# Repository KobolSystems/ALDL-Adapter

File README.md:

## USB ALDL Adapter 

### **Project**: ALDL to USB Adapter 

<!-- Repo Cover Image -->

<!-- Repo Stats -->

<!-- Other Intro -->
### What is a ALDL
Assembly Line Diagnostic Link or ALDL is a proprietary on-board diagnostics system developed by General Motors before the standardization of OBD-2. It was previously called Assembly Line Communications Link or ALCL. The two terms are used interchangeably.

This system was only vaguely standardized and suffered from the fact that specifications for the communications link varied from one model to the next. ALDL was largely used by manufacturers for diagnostics at their dealerships and official maintenance facilities. The connector is usually located under the dash on the driver's side of left-hand drive (LHD) vehicles, though this location was not standardized.

The earliest implementations of ALDL were unidirectional and transmitted serial data at 160 baud using PWM. Some 160 baud models constantly transmitted sensor data on startup, while others started transmitting data when placed in diagnostic mode with a resistor connected to the ALDL port.

Later versions were bidirectional and operated at a much faster (but incredibly slow compared to today's standards) rate of 8192 baud. Implementations using the 8192 baud rate were primarily request-driven, meaning that the main diagnostic data was not transmitted until a request was made. Some idle data transmission of trivial parameters, however, existed in many vehicles. Bidirectional communication also allowed many other functions to be performed via ALDL, such as actuator tests, parameter overrides, and in some cases even reprogramming of the ECU itself. Multiple devices could be placed on the ALDL data line for primitive networking and communication. Many later 8192 baud vehicles, for example, had airbag control, ABS, and even climate control units sending data on the same serial bus.

In both versions, ALDL data is sent in a format unique to the model of ECU in the vehicle with little standardization between models, so a proper definition of the data is required to interpret it. Most professional scan tools require a large database of vehicle definitions.

The signaling of ALDL is similar to the RS-232 serial data standard; differing in the voltages used to denote logical one (usually 0 V DC) and logical zero (either +5 V DC or +12 V DC), and that unlike RS-232, both transmit and receive functions are on the same conductor. Schematics are available on the internet for devices that can be used to convert the ALDL voltages to those of the RS-232 standard, allowing the raw data to be read with a computer having a serial port and the proper software.

<!-- Version History -->
### Version History
|	Version	|	Status	|
|---------------|---------------|
|V.1.0		|Superseded	|
|V.2.0		|In Production	|

<!-- To Do List -->
### Project To Do List
- [ ] List Items Here

### Repo To Do List
- [x] Add V1.0 to Repo
- [ ] Add V1.0 Backplane to Repo
- [ ] Add V2.0 to Repo

<!-- Licencing Always at the Bottom -->
### Licencing 

**Creative Commons: Attribution - NonCommercial - ShareAlike 4.0 International (CC BY-NC-SA 4.0)**

**You are free to:**

**Share** — copy and redistribute the material in any medium or format

**Adapt** — remix, transform, and build upon the material

**Under the following terms:**

**Attribution** — You must give appropriate credit, provide a link to the license, and indicate if changes were made. You may do so in any reasonable manner, but not in any way that suggests the licensor endorses you or your use.

**NonCommercial** — You may not use the material for commercial purposes.

**ShareAlike** — If you remix, transform, or build upon the material, you must distribute your contributions under the same license as the original.

No additional restrictions — You may not apply legal terms or technological measures that legally restrict others from doing anything the license permits.

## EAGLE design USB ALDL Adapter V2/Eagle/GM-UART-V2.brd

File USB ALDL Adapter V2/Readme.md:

## USB ALDL Adapter V2.0  

### **Project**: ALDL to USB Adapter 

<!-- Repo Cover Image -->

<!-- PCB Image -->

### Adapter PCB

### PCB Bill of Materials
Part  |Value      |Device     	|Package          |Description                          	|Mouser Part 	     	|
------|-----------|-------------|-----------------|-----------------------------------------|-----------------------|
C1    |100nF      |C-EUC0603K 	|C0603K           |MLCC - SMD/SMT 100nF 50V               	|603-CC603ZPY5V9BB104   |   
C2    |10nF       |C-EUC0603K 	|C0603K           |MLCC - SMD/SMT 10nF 50V X7R 10%        	|603-CC603KRX7R9BB103   |   
C3    |47pF       |C-EUC0603K 	|C0603K           |MLCC - SMD/SMT 47pF 5% 50V             	|791-MT18N470J500CT     |   
C4    |47pF       |C-EUC0603K 	|C0603K           |MLCC - SMD/SMT 47pF 5% 50V             	|791-MT18N470J500CT     |   
D1    |1N4148     |1N4148W-E3-18|SOD-123	  	  |Diode 100 Volt 500mA 4ns					|78-1N4148W-E3-18       |                              
IC1   |FT230XQ    |FT230XQ    	|QFN16            |USB to BASIC UART IC                   	|895-FT230XQ-R          |                            
R1    |1KR        |R-US_M0805 	|M0805            |Resistor - SMD 1/4watts 1Kohms 1%      	|660-RK73H2ATTD1001F    |   
R3    |27R        |R-US_R0603 	|R0603            |Resistor - SMD 1/20watt 27ohms 5%      	|71-CRCW020127R0JNED    |   
R4    |27R        |R-US_R0603	|R0603            |Resistor - SMD 1/20watt 27ohms 5%      	|71-CRCW020127R0JNED    |   
SV1   |USB-CONN   |MA04-1     	|MA04-1           |PIN HEADER                             	|NOT POPULATED          |  
U$1   |OBD2       |OBD2       	|OBD2             |OBDII Connector                        	|NOT POPULATED		    |     

<!-- To Do List -->
### Repo To Do List
- [x] Create Readme.md
- [ ] Update Readme Image to Actual V2
- [x] Add Eagle Files
- [x] Add .PDF Schematic
- [ ] Add Board Pics

<!-- Licencing Always at the Bottom -->
### Licencing 

**Creative Commons: Attribution - NonCommercial - ShareAlike 4.0 International (CC BY-NC-SA 4.0)**

**You are free to:**

**Share** — copy and redistribute the material in any medium or format

**Adapt** — remix, transform, and build upon the material

**Under the following terms:**

**Attribution** — You must give appropriate credit, provide a link to the license, and indicate if changes were made. You may do so in any reasonable manner, but not in any way that suggests the licensor endorses you or your use.

**NonCommercial** — You may not use the material for commercial purposes.

**ShareAlike** — If you remix, transform, or build upon the material, you must distribute your contributions under the same license as the original.

No additional restrictions — You may not apply legal terms or technological measures that legally restrict others from doing anything the license permits.

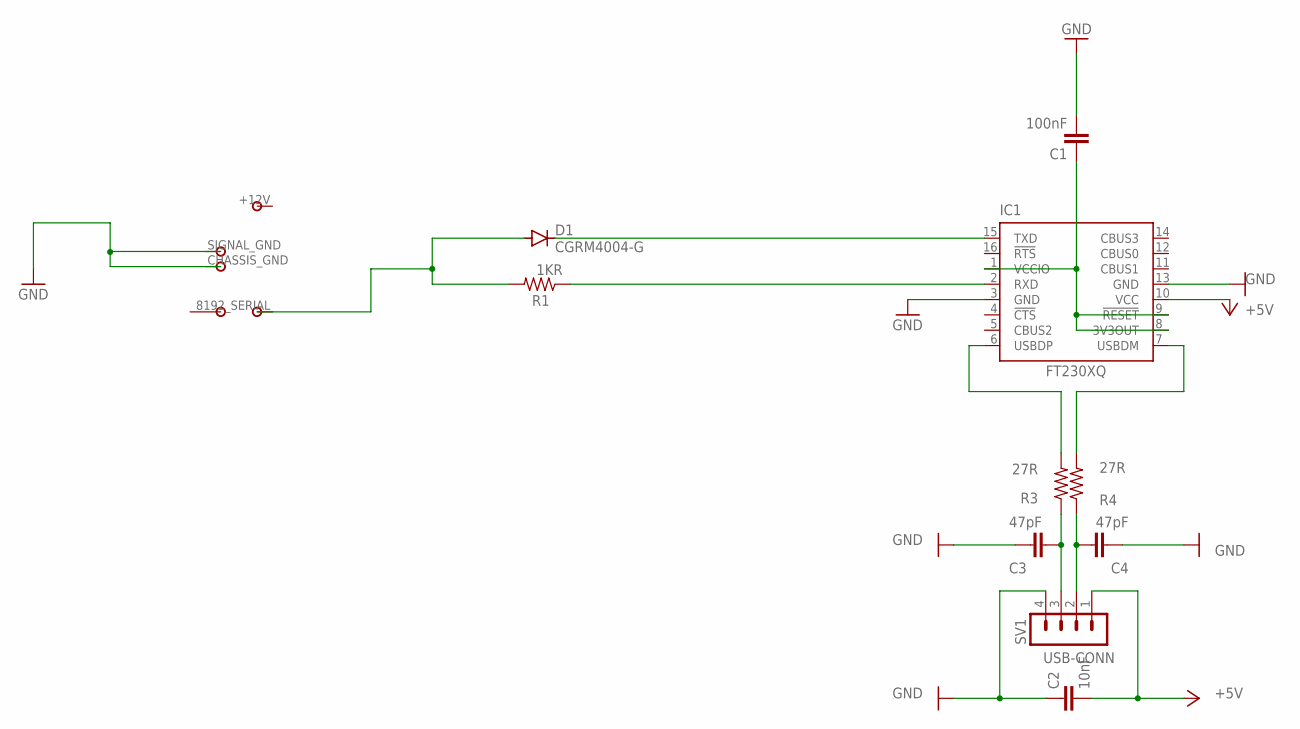
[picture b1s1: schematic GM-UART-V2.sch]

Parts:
C1: 100nF; C0603K
C2: 10nF; C0603K
C3, C4: 47pF; C0603K
D1: CGRM4004-G; SOD-123_MINI-SMA
IC1: FT230XQ; QFN16
R1: 1KR; M0805
R3, R4: 27R; R0603
SV1: USB-CONN; MA04-1
U$2: OBD2PLUG

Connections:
+5V: C2.2, IC1.10 (VCC), SV1.1
+12V: U$2.+12V
GM-UART: D1.A, R1.2, U$2.8192_SERIAL
GND: C1.2, C2.1, C3.2, C4.2, IC1.3 (GND), IC1.13 (GND), SV1.4, U$2.CHASSIS_GND, U$2.SIGNAL_GND
unnamed: C1.1, IC1.1 (VCCIO), IC1.8 (3V3OUT), IC1.9 (!RESET)
unnamed: C3.1, R3.1, SV1.3
unnamed: C4.1, R4.1, SV1.2
unnamed: IC1.7 (USBDM), R4.2
unnamed: IC1.6 (USBDP), R3.2
RXD: IC1.2 (RXD), R1.1
TXD: D1.C, IC1.15 (TXD)

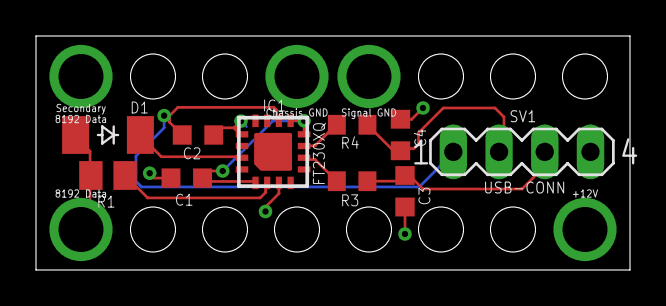
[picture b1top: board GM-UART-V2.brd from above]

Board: 2 copper layers, 33.0 x 13.0 mm, 11 parts (0 on the bottom side), 10 nets.

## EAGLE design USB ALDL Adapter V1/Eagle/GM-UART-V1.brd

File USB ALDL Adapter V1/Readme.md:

## USB ALDL Adapter V1.0  

### **Project**: ALDL to Bluetooth Adapter using a Mini Computing Board 

<!-- Repo Cover Image -->

<!-- Other Intro -->
### What is a ALDL
Assembly Line Diagnostic Link or ALDL is a proprietary on-board diagnostics system developed by General Motors before the standardization of OBD-2. It was previously called Assembly Line Communications Link or ALCL. The two terms are used interchangeably.

This system was only vaguely standardized and suffered from the fact that specifications for the communications link varied from one model to the next. ALDL was largely used by manufacturers for diagnostics at their dealerships and official maintenance facilities. The connector is usually located under the dash on the driver's side of left-hand drive (LHD) vehicles, though this location was not standardized.

The earliest implementations of ALDL were unidirectional and transmitted serial data at 160 baud using PWM. Some 160 baud models constantly transmitted sensor data on startup, while others started transmitting data when placed in diagnostic mode with a resistor connected to the ALDL port.

Later versions were bidirectional and operated at a much faster (but incredibly slow compared to today's standards) rate of 8192 baud. Implementations using the 8192 baud rate were primarily request-driven, meaning that the main diagnostic data was not transmitted until a request was made. Some idle data transmission of trivial parameters, however, existed in many vehicles. Bidirectional communication also allowed many other functions to be performed via ALDL, such as actuator tests, parameter overrides, and in some cases even reprogramming of the ECU itself. Multiple devices could be placed on the ALDL data line for primitive networking and communication. Many later 8192 baud vehicles, for example, had airbag control, ABS, and even climate control units sending data on the same serial bus.

In both versions, ALDL data is sent in a format unique to the model of ECU in the vehicle with little standardization between models, so a proper definition of the data is required to interpret it. Most professional scan tools require a large database of vehicle definitions.

The signaling of ALDL is similar to the RS-232 serial data standard; differing in the voltages used to denote logical one (usually 0 V DC) and logical zero (either +5 V DC or +12 V DC), and that unlike RS-232, both transmit and receive functions are on the same conductor. Schematics are available on the internet for devices that can be used to convert the ALDL voltages to those of the RS-232 standard, allowing the raw data to be read with a computer having a serial port and the proper software.

### PCB Bill of Materials
Part	|	Value	|	Part Number	|	Qty	|
--------|---------------|-----------------------|---------------|
C1	|	10nF	|	885012205031	|	1	|
C2,C3	|	47pF	|	VJ0402A470JXXCW1BC|	2	|
C4	|	100nF	|	885012105018	|	1	|
D1	|	150mA	|	1N4148X-TP	|	1	|
R1	|	1KR	|	RC0402FR-071KL	|	1	|
R2	|		|	PMS0603-025	|	1	|
R3,R4	|	27R 	|	RC0402FR-0727RL	|	2	|
SV1	|	9 pin	|	200-HTMS11002TSRA|	1	|
X1	|		|	10033526-N3212LF| 	1	|
IC1	|		|	FT230XS-R	|	1 	|
Shell	|		|	AOT-1127 - Black|	1	|
USB	|	Cable	|	571-1496476-6	|	1	|
PCB	|		|	PCB Manufacture	|	1	|

<!-- To Do List -->
### Project To Do List
- [ ] More to add as I think of it
- [ ] List Items Here

### Repo To Do List
- [ ] Update Readme Image to Actual V1
- [ ] Add Backplane to Repo
- [ ] More to add as i think of it

<!-- Licencing Always at the Bottom -->
### Licencing 

**Creative Commons: Attribution - NonCommercial - ShareAlike 4.0 International (CC BY-NC-SA 4.0)**

**You are free to:**

**Share** — copy and redistribute the material in any medium or format

**Adapt** — remix, transform, and build upon the material

**Under the following terms:**

**Attribution** — You must give appropriate credit, provide a link to the license, and indicate if changes were made. You may do so in any reasonable manner, but not in any way that suggests the licensor endorses you or your use.

**NonCommercial** — You may not use the material for commercial purposes.

**ShareAlike** — If you remix, transform, or build upon the material, you must distribute your contributions under the same license as the original.

No additional restrictions — You may not apply legal terms or technological measures that legally restrict others from doing anything the license permits.

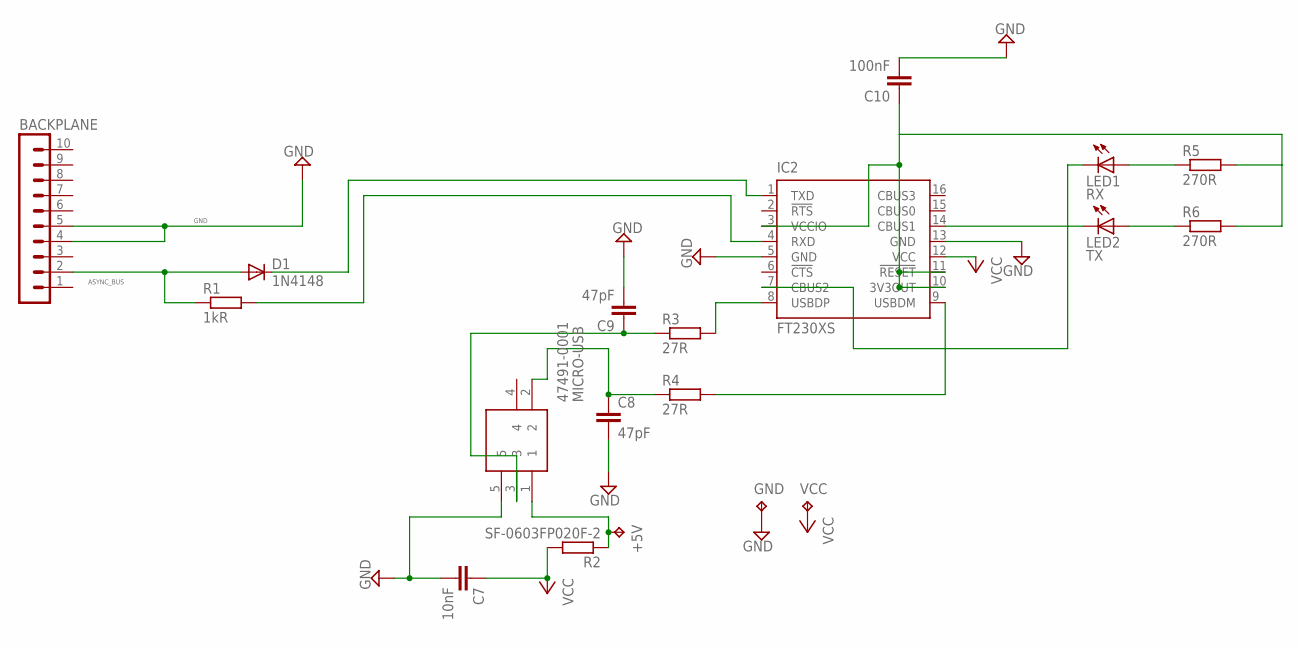
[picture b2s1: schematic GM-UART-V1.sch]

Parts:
+5V: VCC-Unfused; TP14SQ
BACKPLANE: MA10-1
C7: 10nF; C0402
C8, C9: 47pF; C0402
C10: 100nF; C0402
D1: 1N4148; SOD523
GND: TPTP14SQ; TP14SQ
IC2: FT230XS; SSOP16
LED1: RX; LED3MM
LED2: TX; LED3MM
MICRO-USB: 47491-0001
R1: 1kR; R0402
R2: SF-0603FP020F-2; R0603
R3, R4: 27R; R0402
R5, R6: 270R; 0207/10
VCC: VCC-Fused; TP14SQ

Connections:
ASYNC_BUS: BACKPLANE.2, D1.A, R1.1
GND: BACKPLANE.4, BACKPLANE.5, C7.2, C8.2, C9.2, C10.2, GND.TP, IC2.5 (GND), IC2.13 (GND), MICRO-USB.5
unnamed: +5V.TP, MICRO-USB.1, R2.1
unnamed: LED1.A, R5.1
unnamed: LED2.A, R6.1
unnamed: C10.1, IC2.3 (VCCIO), IC2.10 (3V3OUT), IC2.11 (!RESET), R5.2, R6.2
unnamed: IC2.8 (USBDP), R3.2
unnamed: IC2.9 (USBDM), R4.2
RX: IC2.4 (RXD), R1.2
RX-LED: IC2.7 (CBUS2), LED1.K (C)
TX: D1.C, IC2.1 (TXD)
TX-LED: IC2.14 (CBUS1), LED2.K (C)
USBDM: C8.1, MICRO-USB.2, R4.1
USBDP: C9.1, MICRO-USB.3, R3.1
VCC: C7.1, IC2.12 (VCC), R2.2, VCC.TP

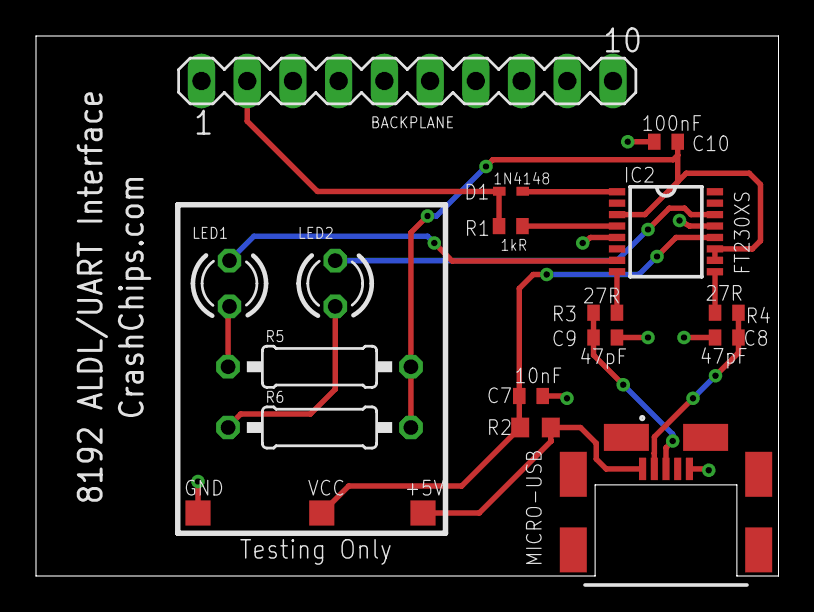
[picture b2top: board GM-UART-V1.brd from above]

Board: 2 copper layers, 41.2 x 30.0 mm, 19 parts (0 on the bottom side), 15 nets.

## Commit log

2020-12-03 inital upload
2022-07-31 Research for BT Version

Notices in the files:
README.md:
License: CC-BY-NC-SA-4.0
